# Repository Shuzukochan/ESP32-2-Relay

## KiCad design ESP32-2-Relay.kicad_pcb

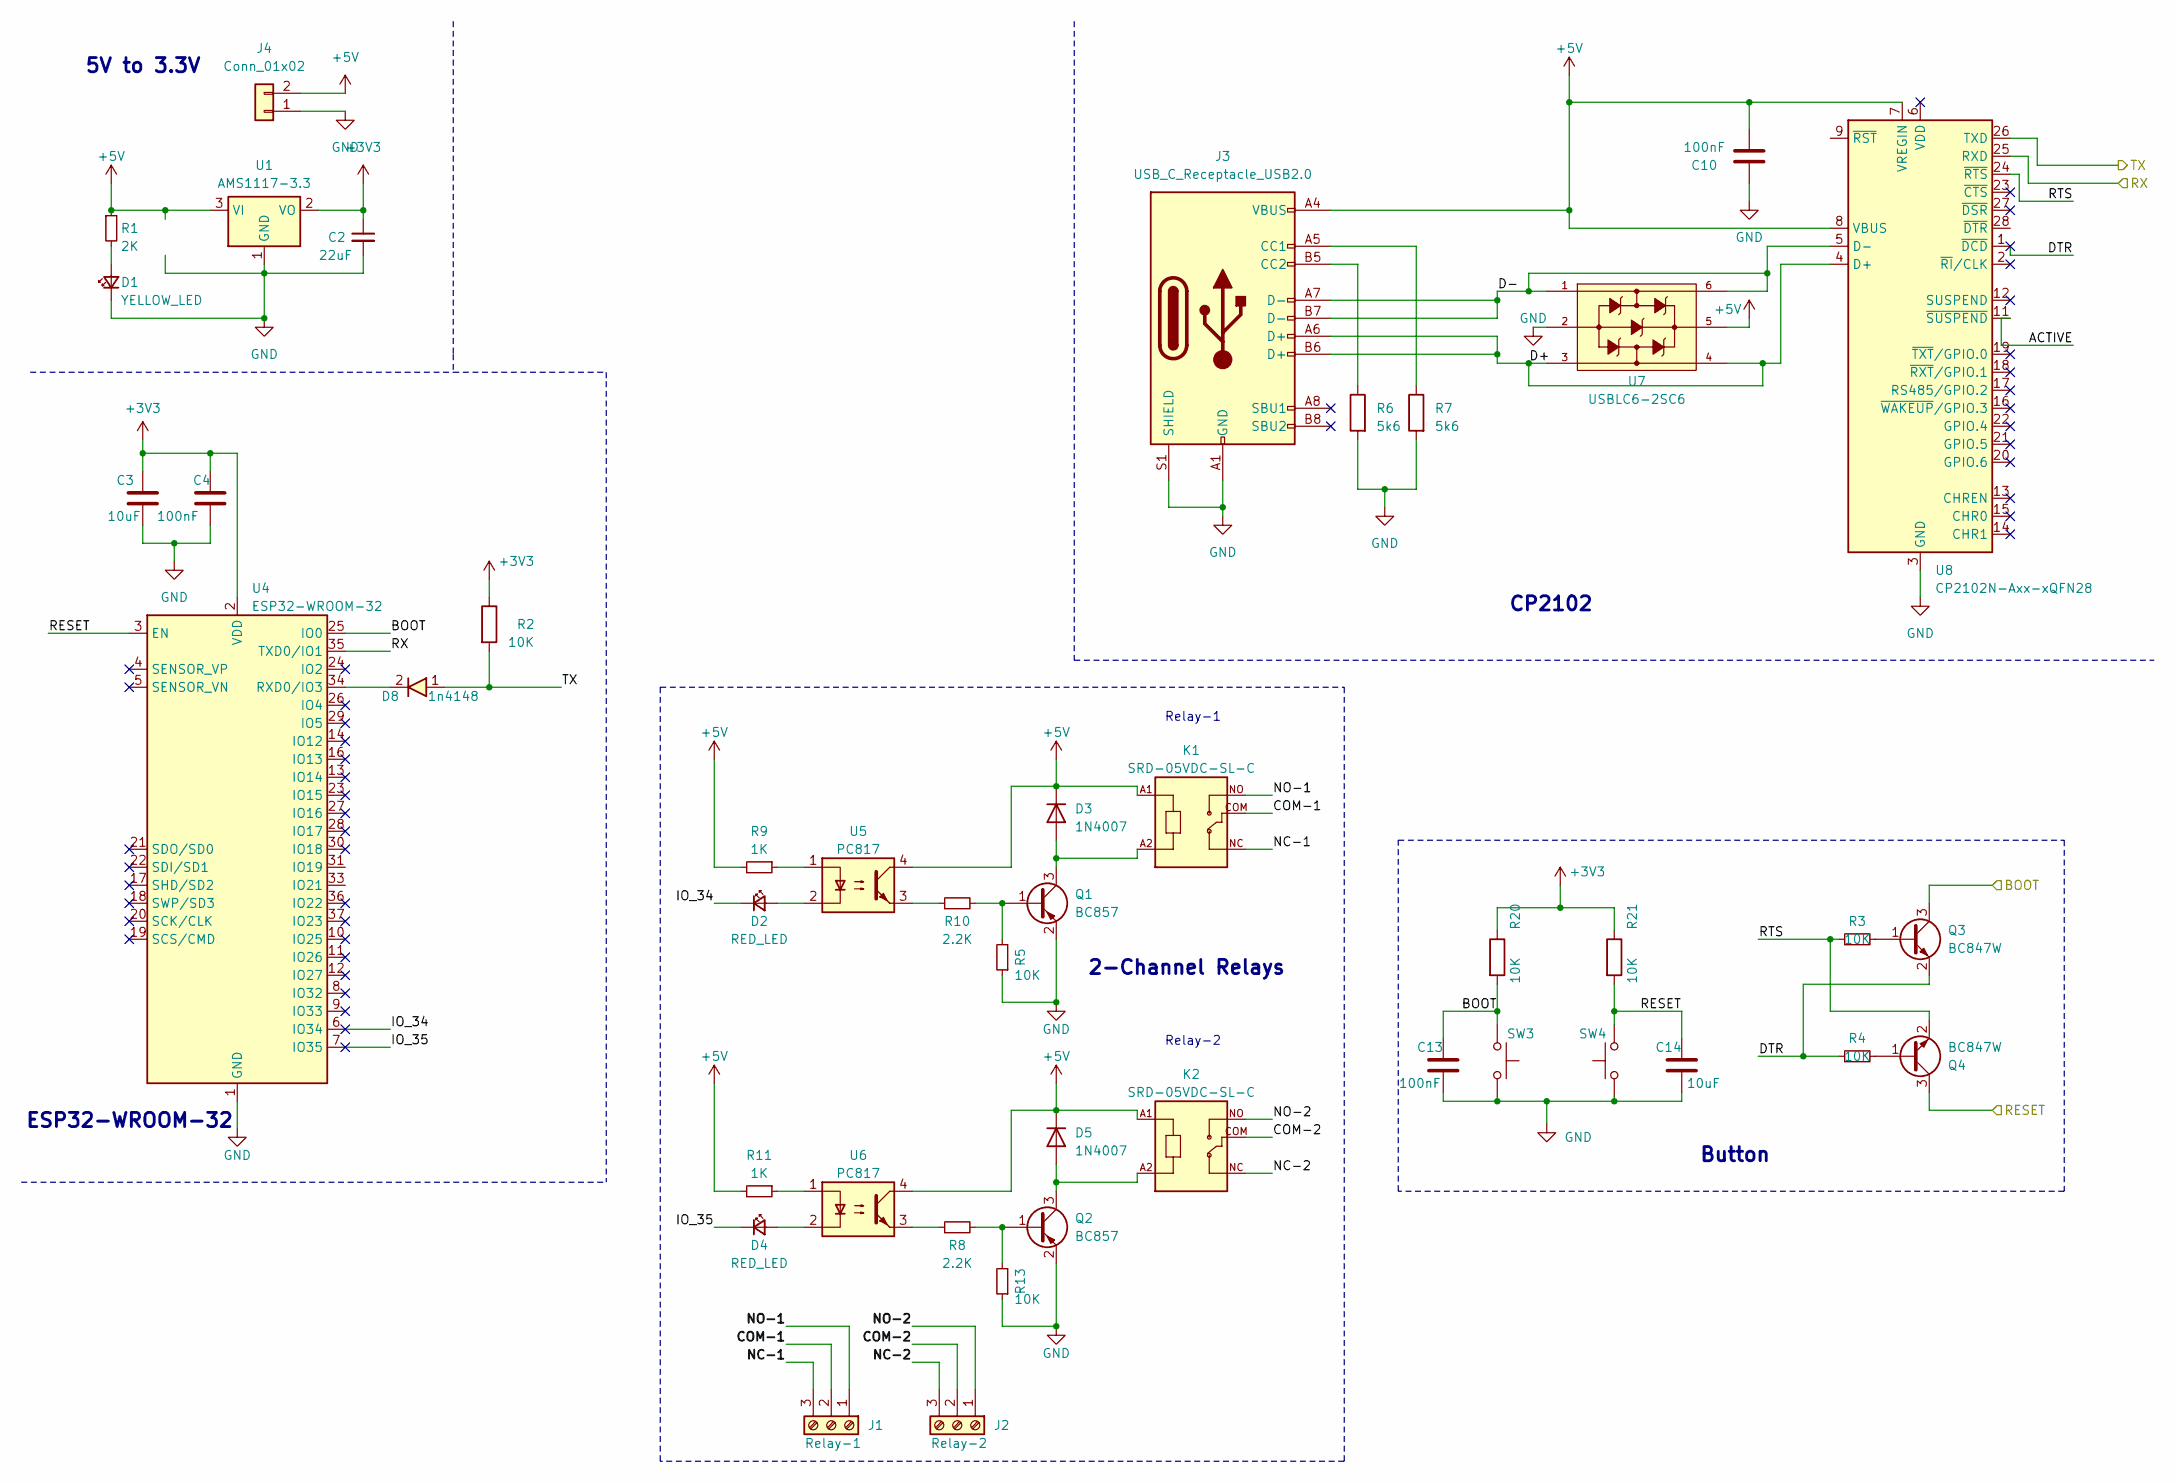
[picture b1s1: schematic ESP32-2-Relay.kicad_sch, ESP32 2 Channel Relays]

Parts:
C2: 22uF; C_0201_0603Metric
C3, C14: 10uF; C_0201_0603Metric
C4, C10, C13: 100nF; C_0201_0603Metric
D1: YELLOW_LED; LED_0201_0603Metric
D2, D4: RED_LED; LED_0201_0603Metric
D3, D5: 1N4007; D_SMA
D8: 1n4148; D_SOD-123
J1: Relay-1; TerminalBlock_Phoenix_MKDS-1,5-3-5.08_1x03_P5.08mm_Horizont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
J2: Relay-2; TerminalBlock_Phoenix_MKDS-1,5-3-5.08_1x03_P5.08mm_Horizont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
J3: USB_C_Receptacle_USB2.0; USB_C_Receptacle_GCT_USB4105-xx-A_16P_TopMnt_Horizontal
J4: Conn_01x02; Conn_XH-P2.54mm-2P
K1, K2: SRD-05VDC-SL-C; RELAY_SRD-05VDC-SL-C
Q1, Q2: BC857; TSOT-23
Q3, Q4: BC847W; SOT-323_SC-70
R1: 2K; R_0603_1608Metric
R2, R3, R4, R5, R13, R20, R21: 10K; R_0603_1608Metric
R6, R7: 5k6; R_0805_2012Metric
R8, R10: 2.2K; R_0805_2012Metric
R9, R11: 1K; R_0603_1608Metric
SW3, SW4: SW_Push; SW_Tactile_SPST_NO_Straight_CK_PTS636Sx25SMTRLFS
U1: AMS1117-3.3; SOT-223-3_TabPin2
U4: ESP32-WROOM-32
U5, U6: PC817; SMDIP-4_W7.62mm
U7: USBLC6-2SC6; SOT-23-6
U8: CP2102N-Axx-xQFN28; QFN-28-1EP_5x5mm_P0.5mm_EP3.35x3.35mm

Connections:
+3V3: C2.1, C3.1, C4.1, R2.1, R20.1, R21.1, U1.2 (VO), U4.2 (VDD)
+5V: C10.2, D3.1 (K), D5.1 (K), J3.A4 (VBUS), J3.A9 (VBUS), J3.B4 (VBUS), J3.B9 (VBUS), J4.2, K1.A1, K2.A1, R1.1, R9.2, R11.2, U1.3 (VI), U5.4, U6.4, U7.5, U8.7 (VREGIN), U8.8 (VBUS); also elsewhere on the board
/ACTIVE: U8.11 (~SUSPEND)
/BOOT: C13.1, Q3.3 (C), R20.2, SW3.1, U4.25 (IO0)
/COM-1: J1.2, K1.COM
/COM-2: J2.2, K2.COM
/D+: J3.A6 (D+), J3.B6 (D+), U7.3, U7.4, U8.4 (D+)
/D-: J3.A7 (D-), J3.B7 (D-), U7.1, U7.6, U8.5 (D-)
/DTR: Q3.2 (E), R4.1, U8.1 (~DCD)
/IO_34: D2.1 (K), U4.6 (IO34)
/IO_35: D4.1 (K), U4.7 (IO35)
/NC-1: J1.3, K1.NC
/NC-2: J2.3, K2.NC
/NO-1: J1.1, K1.NO
/NO-2: J2.1, K2.NO
/RESET: C14.1, Q4.3 (C), R21.2, SW4.2, U4.3 (EN)
/RTS: Q4.2 (E), R3.1, U8.24 (~RTS)
/RX: U4.35 (TXD0/IO1), U8.25 (RXD)
/TX: D8.1, R2.2, U8.26 (TXD)
GND: C2.2, C3.2, C4.2, C10.1, C13.2, C14.2, D1.1 (K), J3.A1 (GND), J3.A12 (GND), J3.B1 (GND), J3.B12 (GND), J3.S1 (SHIELD), J4.1, Q1.2 (E), Q2.2 (E), R5.1, R6.2, R7.2, R13.1, SW3.2, SW4.1, U1.1 (GND), U4.1 (GND), U4.15 (GND), U4.38 (GND), U4.39 (GND), U7.2, U8.3 (GND), U8.29 (GND); also elsewhere on the board
unnamed: D1.2 (A), R1.2
unnamed: D2.2 (A), U5.2
unnamed: D3.2 (A), K1.A2, Q1.3 (C)
unnamed: D4.2 (A), U6.2
unnamed: D5.2 (A), K2.A2, Q2.3 (C)
unnamed: J3.A5 (CC1), R7.1
unnamed: J3.B5 (CC2), R6.1
unnamed: Q1.1 (B), R5.2, R10.2
unnamed: Q2.1 (B), R8.2, R13.2
unnamed: Q3.1 (B), R3.2
unnamed: Q4.1 (B), R4.2
unnamed: R8.1, U6.3
unnamed: R9.1, U5.1
unnamed: R10.1, U5.3
unnamed: R11.1, U6.1
unnamed: D8.2, U4.34 (RXD0/IO3)

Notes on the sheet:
5V to 3.3V
2-Channel Relays
Button
Relay-1
Relay-2
ESP32-WROOM-32
CP2102

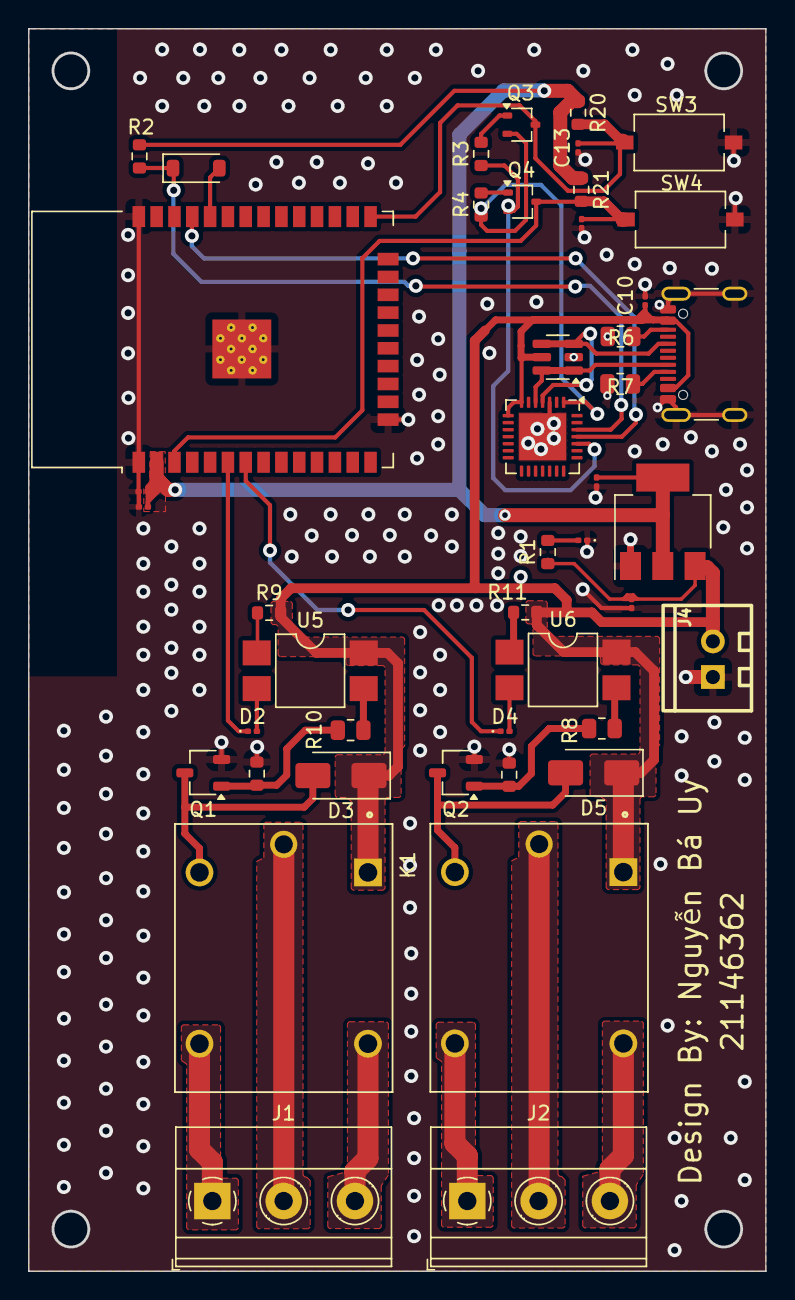
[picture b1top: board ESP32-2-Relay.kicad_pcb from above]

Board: 2 copper layers, 52.5 x 88.5 mm, 45 parts (0 on the bottom side), 35 nets.

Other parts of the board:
C1: 22uF; C_0201_0603Metric

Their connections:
+5V: C1.1; also elsewhere on the board
GND: C1.2; also elsewhere on the board

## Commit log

2024-11-20 done
2024-11-23 lastest
